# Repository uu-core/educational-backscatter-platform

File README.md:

# Pico-Backscatter
An educational project on backscatter using Raspberry Pi Pico

## Repo Organization
- `hardware` contains the hardware design with further description and explanation (generating the PIO using the python script).
- `project_pico_libs` contains the libs for all projects using the RPI Pico (carrier/receiver/baseband).
- `baseband` contains a 2-FSK baseband code using Pico PIO together with a generator script, its description and some exercise questions.
- `carrier-CC2500` contains a carrier generator using the Mikroe-1435 (CC2500) on the Pico.
- `receiver-CC2500` contains a receiver using the Mikroe-1435 (CC2500) on the Pico.
- `carrier-Firefly` contains the configuration guidance for home setup with zolertia firefly as carrier.
- `carrier-characteristics` contains a measurement to estimate the typical carrier bandwidth.
- `carrier_receiver-CC1352` contains the configuration guidance for lab setup with CC1352 as carrier and/or receiver.
- `carrier-receiver-baseband` integrates all components into one setup: the Pico generates the baseband, uses one Mikroe-1435 (CC2500) to generate a carrier and a second Mikroe-1435 (CC2500) to receive the backscattered signal.
- `stats` contains the system evaluation script.

## Installation
A number of pre-requisites are needed to work with this repo:
Raspberry Pi Pico SDK, cmake and arm-none-eabi-gcc have to be installed for building and flashing the application code.
<br>Please follow the installation guidance in [Getting started with Rasberry Pi Pico](https://datasheets.raspberrypi.com/pico/getting-started-with-pico.pdf).
<br>Using Visual Studio Code is recommended.

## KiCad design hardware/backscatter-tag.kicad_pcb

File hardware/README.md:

# Pico-Backscatter: frontend
The implementation for the backscatter tag frontend on a four-layer FR4 PCB with 1oz copper thickness and a spacing of 0.2mm between the top and first inner layer for 50 ohm impedance matching.

### Usage notes
- The board can be used with the Maker Pi Pico (bottom connectors) or the Raspberry Pi Pico (top connectors). _Do not connect a RPI Pico and Maker Pi Pico at the same time._
- For power measurements, a power profiler can be connected to J5. Remember that the board should not be powered by two sources at the same time. Therefore, _unplug the USB from the RPI Pico before using an external power supply, such as a power profiler_. Just in case that two supplies get connected at the same time, they are be protected by a schottky diode. Therefore the board is supplied with about 0.25V less than provided (the voltage drop can be avoided by: supplying the voltage directly to the VSYS pin rather than J5, which avoids the diode and is therefore unprotected. Another alternative is to replace the diode with a mosfet in standard reverse voltage protection configuration).
- The board provides an interface to four SMA connectors for backscattering signals. This enables the use of antenna arrays and the resulting directivity/gain of different configurations can be generated using [Matlab's Antenna array design tool](https://se.mathworks.com/help/antenna/gs/design-and-analysis-using-antenna-array-designer-app.html).
- The board provides two connections for the ccRF click boards (Mikroe-1435 with the CC2500). They can be used as carrier generator and receiver.
- Notice that you can simulate a larger distance to the carrier by decreasing the transmission power in a static setup.

### Technical notes
- Each antenna is connected to an open or closed circuit based on a signal of the RPI Pico. This results in a reflection coefficient of +1 or -1, such that the incoming signal is always fully reflected either in phase (0°) or inverted (at 180° phase). In the time domain, we can think of this as taking the carrier and multiplying it with a sequence of +1/-1, which is equivalent to a convolution in the frequency domain and can therefore be used as modulation.
- Consider an ambient carrier signal $f_c$ and the RPI Pico generating a baseband signal $f_b$, which controls the antenna switch. The backscattered signal will then be $f_{s} = f_c + f_b$. Since we have control of $f_b$, we can use $f_s$ directly to generate a Frequency-Shift Keying (FSK) or On-Off Keying (OOK). Since additionally the phase of the carrier is static, the phase of the backscattered signal $f_s$ is equal to the phase of the baseband signal $f_b$. This can be used to generate a Phase-Shift Keying (PSK). For example, increasing the frequency of $f_b$ by 1 MHz and changing its phase by 90°, will also change the frequency and phase of the backscattered signal $f_s$ by 1 MHz and phase of 90°. Finally, due to the spectrum of a sinus, we obtain a second (mirrored) image of $f_s$ at $f_m = f_c - f_b$ which we can ignore for now. Since the baseband signal is also a square-wave and not a sinus, the backscattered signal will have harmonic overtones above $f_s$ and below $f_m$, which we can also ignore for now. However, you can find the mirrored image on the spectrum analyzer and also the overtones at a sufficiently large Signal-to-Noise ratio (SNR).
- The switch that controls the antenna termination could be implemented with a simple MOSFET. However, using an RF-switch provides a better impedance matching and control. Therefore, this platform uses the design of Ambuj Varshney and uses the [HMC190BMS8E](https://www.analog.com/media/en/technical-documentation/data-sheets/hmc190b.pdf). RF-switches can be categorized into having reflective (open circuit) or absorptive ($50 \Omega$ matching) inputs while not being selected to connect to the output. The HMC190BMS8E is a reflective RF-switch. Therefore, we can connect the antenna to its _input_. While the antenna is not selected as input, the RF-switch represents an open circuit (reflection coefficient +1). Now, we can terminate the output of the RF-switch directly to ground to generate the short circuit (reflection coefficient -1). The baseband signal of the RPI Pico controls if the antenna input connects to the output of the RF-switch or not and therefore changes the reflection coefficient at the antenna as described above between +1/-1.

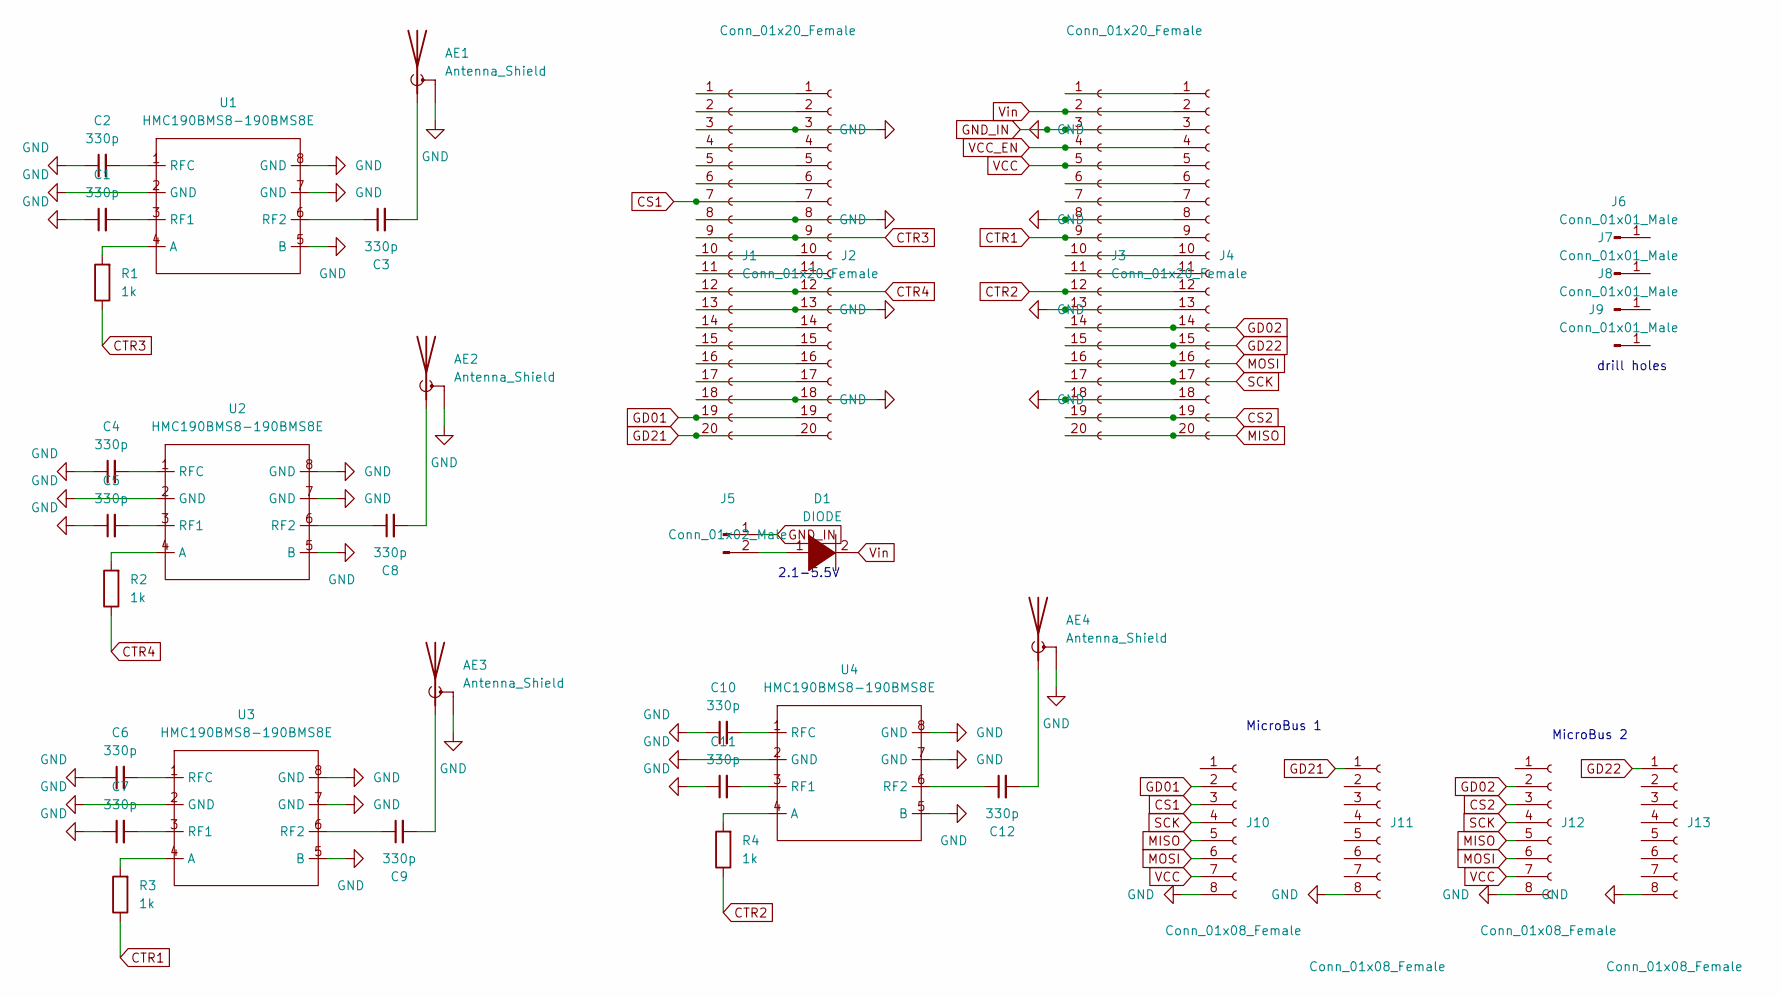
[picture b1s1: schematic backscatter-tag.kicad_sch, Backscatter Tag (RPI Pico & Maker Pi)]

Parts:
AE1, AE2, AE3, AE4: Antenna_Shield; SMA-60312002114503
C1, C2, C3, C4, C5, C6, C7, C8, C9, C10, C11, C12: 330p; C_0402_1005Metric
D1: DIODE; SOD-123FL-2
J1, J2, J3, J4: Conn_01x20_Female; PinSocket_1x20_P2.54mm_Vertical_SMD_Pin1Left
J5: Conn_01x02_Male; PinHeader_1x02_P2.54mm_Vertical
J6, J7, J8, J9: Conn_01x01_Male; mounting-whole
J10, J11, J12, J13: Conn_01x08_Female; PinSocket_1x08_P2.54mm_Vertical
R1, R2, R3, R4: 1k; R_0402_1005Metric
U1, U2, U3, U4: HMC190BMS8-190BMS8E; MSOP8

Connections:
CS1: J1.7, J2.7, J10.3
CS2: J3.19, J4.19, J12.3
CTR1: J3.9, J4.9, R3.1
CTR2: J3.12, J4.12, R4.1
CTR3: J1.9, J2.9, R1.1
CTR4: J1.12, J2.12, R2.1
GD01: J1.19, J2.19, J10.2
GD02: J3.14, J4.14, J12.2
GD21: J1.20, J2.20, J11.1
GD22: J3.15, J4.15, J13.1
GND_IN: AE1.2 (Shield), AE2.2 (Shield), AE3.2 (Shield), AE4.2 (Shield), C1.1, C2.1, C4.1, C5.1, C6.1, C7.1, C10.1, C11.1, J1.3, J1.8, J1.13, J1.18, J2.3, J2.8, J2.13, J2.18, J3.3, J3.8, J3.13, J3.18, J4.3, J4.8, J4.13, J4.18, J5.1, J10.8, J11.8, J12.8, J13.8, U1.2 (GND), U1.5 (B), U1.7 (GND), U1.8 (GND), U2.2 (GND), U2.5 (B), U2.7 (GND), U2.8 (GND), U3.2 (GND), U3.5 (B), U3.7 (GND), U3.8 (GND), U4.2 (GND), U4.5 (B), U4.7 (GND), U4.8 (GND)
MISO: J3.20, J4.20, J10.5, J12.5
MOSI: J3.16, J4.16, J10.6, J12.6
unnamed: AE1.1 (A), C3.2
unnamed: AE2.1 (A), C8.2
unnamed: AE3.1 (A), C9.2
unnamed: AE4.1 (A), C12.2
unnamed: C1.2, U1.3 (RF1)
unnamed: C2.2, U1.1 (RFC)
unnamed: C3.1, U1.6 (RF2)
unnamed: C4.2, U2.1 (RFC)
unnamed: C5.2, U2.3 (RF1)
unnamed: C6.2, U3.1 (RFC)
unnamed: C7.2, U3.3 (RF1)
unnamed: C8.1, U2.6 (RF2)
unnamed: C9.1, U3.6 (RF2)
unnamed: C10.2, U4.1 (RFC)
unnamed: C11.2, U4.3 (RF1)
unnamed: C12.1, U4.6 (RF2)
unnamed: D1.1 (K), J5.2
unnamed: J1.1, J2.1
unnamed: J1.2, J2.2
unnamed: J1.4, J2.4
unnamed: J1.5, J2.5
unnamed: J1.6, J2.6
unnamed: J1.10, J2.10
unnamed: J1.11, J2.11
unnamed: J1.14, J2.14
unnamed: J1.15, J2.15
unnamed: J1.16, J2.16
unnamed: J1.17, J2.17
unnamed: J3.1, J4.1
unnamed: J3.6, J4.6
unnamed: J3.7, J4.7
unnamed: J3.10, J4.10
unnamed: J3.11, J4.11
unnamed: R1.2, U1.4 (A)
unnamed: R2.2, U2.4 (A)
unnamed: R3.2, U3.4 (A)
unnamed: R4.2, U4.4 (A)
SCK: J3.17, J4.17, J10.4, J12.4
VCC: J3.5, J4.5, J10.7, J12.7
VCC_EN: J3.4, J4.4
Vin: D1.2 (A), J3.2, J4.2

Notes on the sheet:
MicroBus 1
drill holes
2.1-5.5V
MicroBus 2

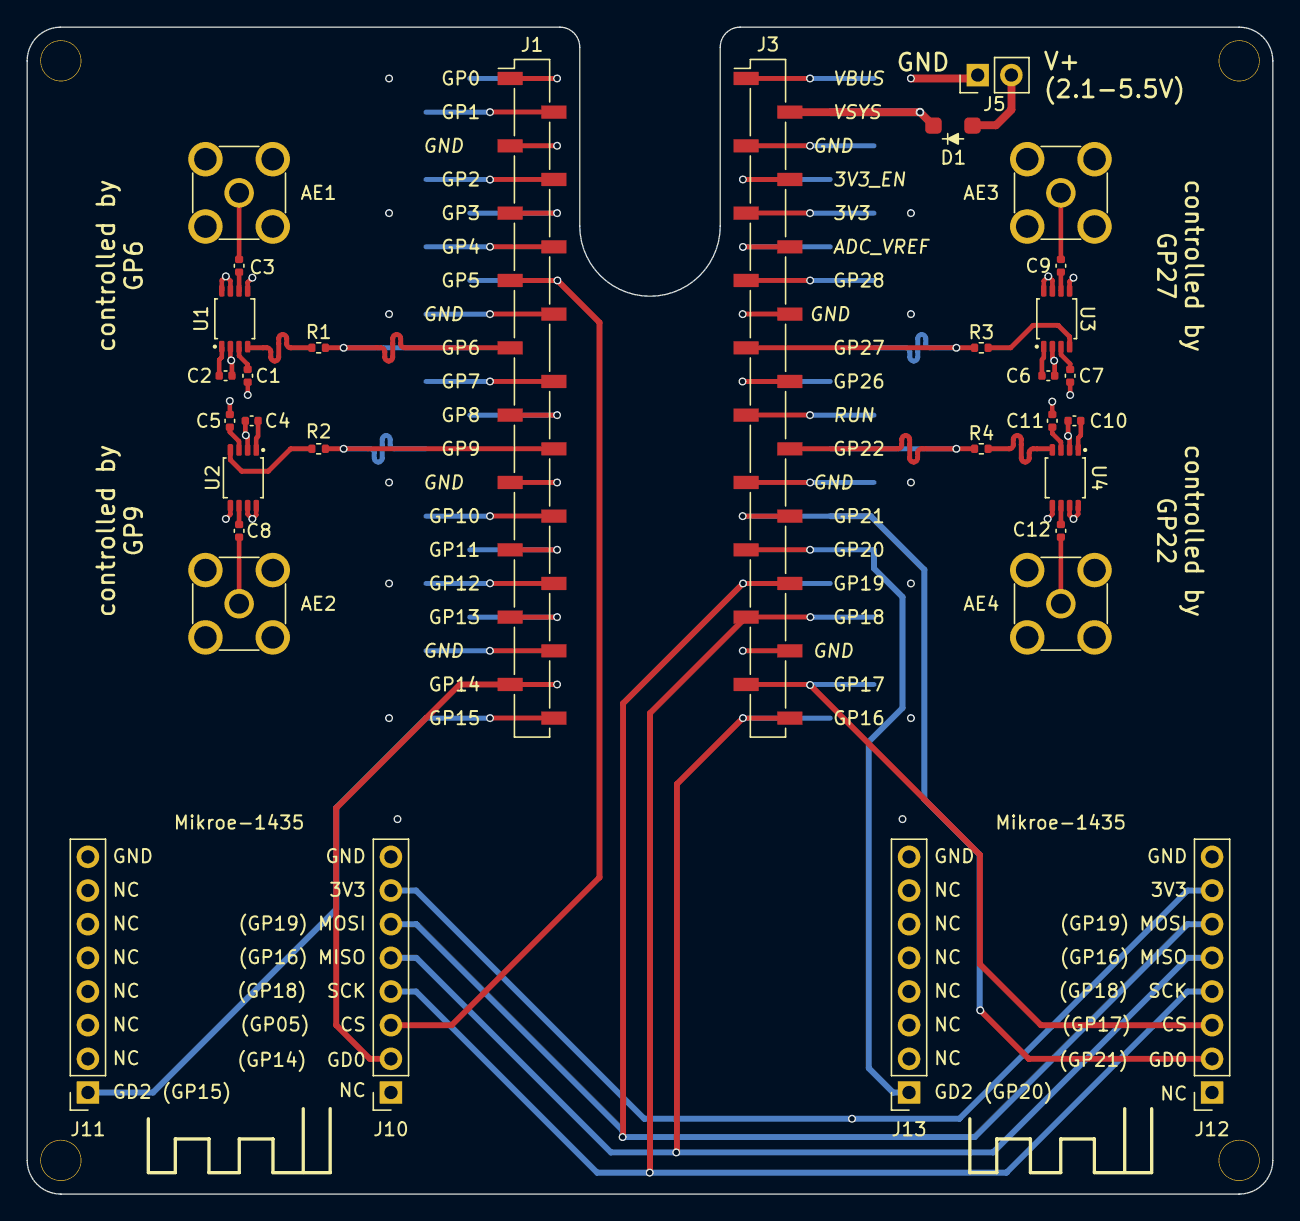
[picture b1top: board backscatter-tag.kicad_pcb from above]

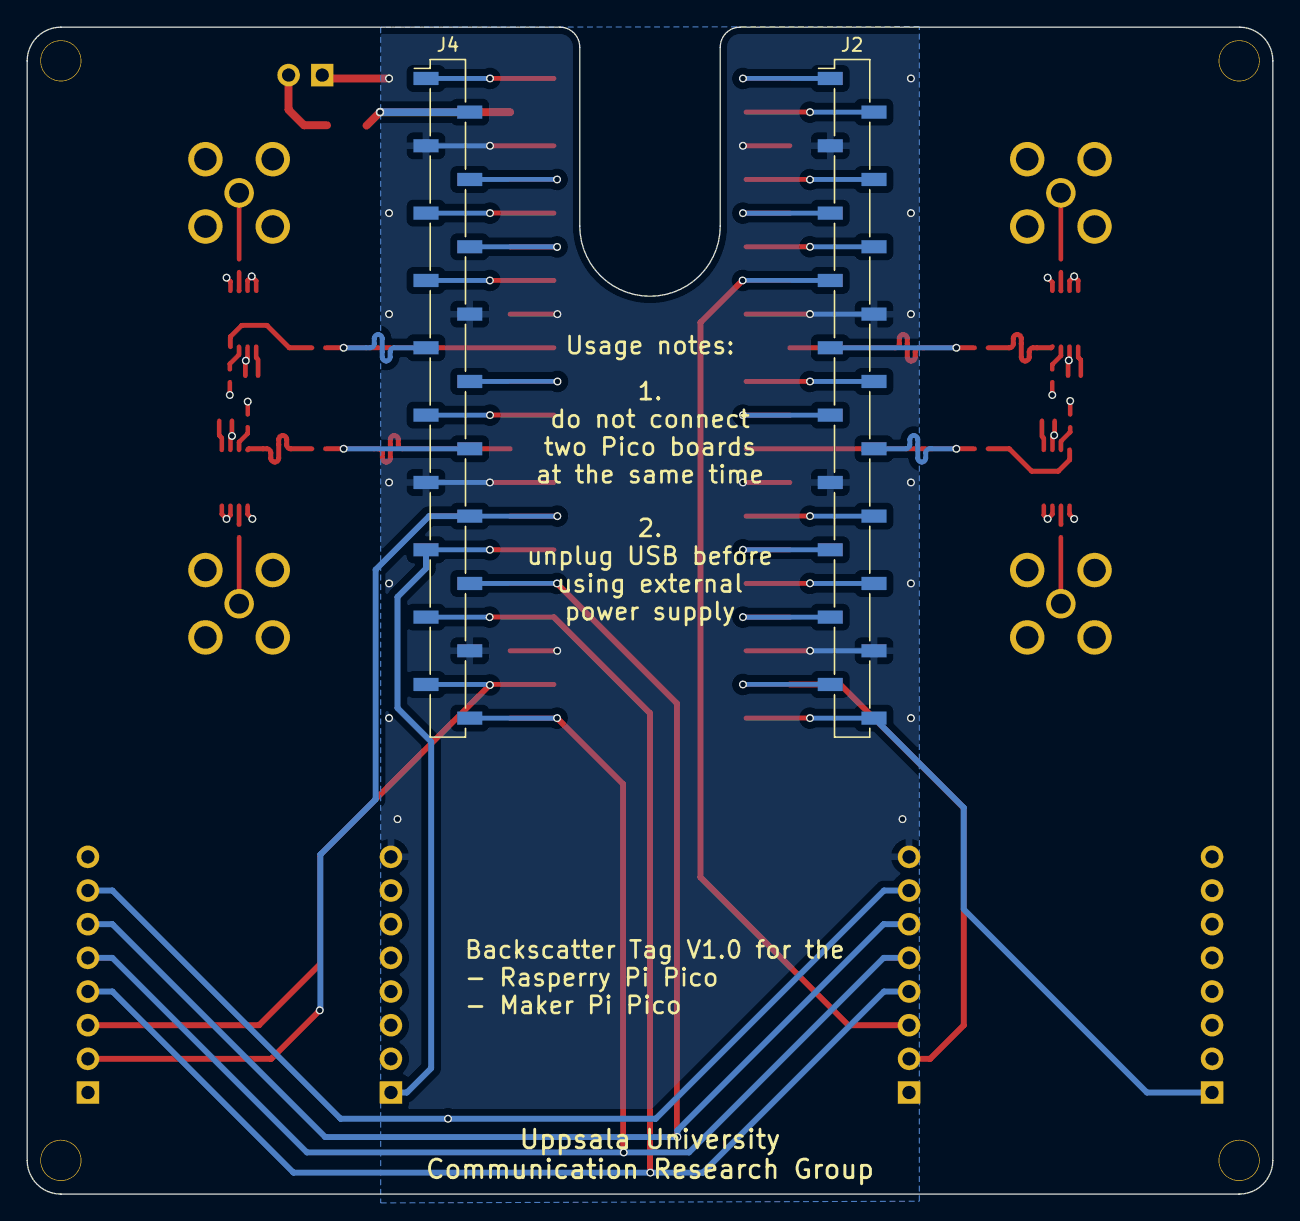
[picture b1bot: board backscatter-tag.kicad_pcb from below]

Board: 4 copper layers, 94.0 x 88.0 mm, 38 parts (2 on the bottom side), 54 nets.

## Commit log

2023-05-15 Repo-setup
2023-05-19 mobisys'23 demo, receiver analysis code with matplotlib animation
2023-05-19 input callback not working
2023-05-19 Moved receiver to core 1.
2023-05-19 working uart interface for dynamically changing baseband and receiver
2023-05-22 test logging and integrate receiver configuration into demo.py, use config.xlsx as configuration file
2023-05-22 for long-time running discard the old value, change the axis to time delta in second unit
2023-05-23 add seq number, consider the missing packets in ber calculation
2023-05-23 precise tx timing + read-out of config
2023-05-24 updates for demo
2023-06-12 the serial reading the analysis script.
2023-06-12 change the print function and hide crc error
2023-06-12 add the script for cc1352
2023-06-12 change cc1352 print function and hide crc error
